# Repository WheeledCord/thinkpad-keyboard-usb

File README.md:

A PCB to allow a thinkpad laptop keyboard to be used as a USB keyboard.

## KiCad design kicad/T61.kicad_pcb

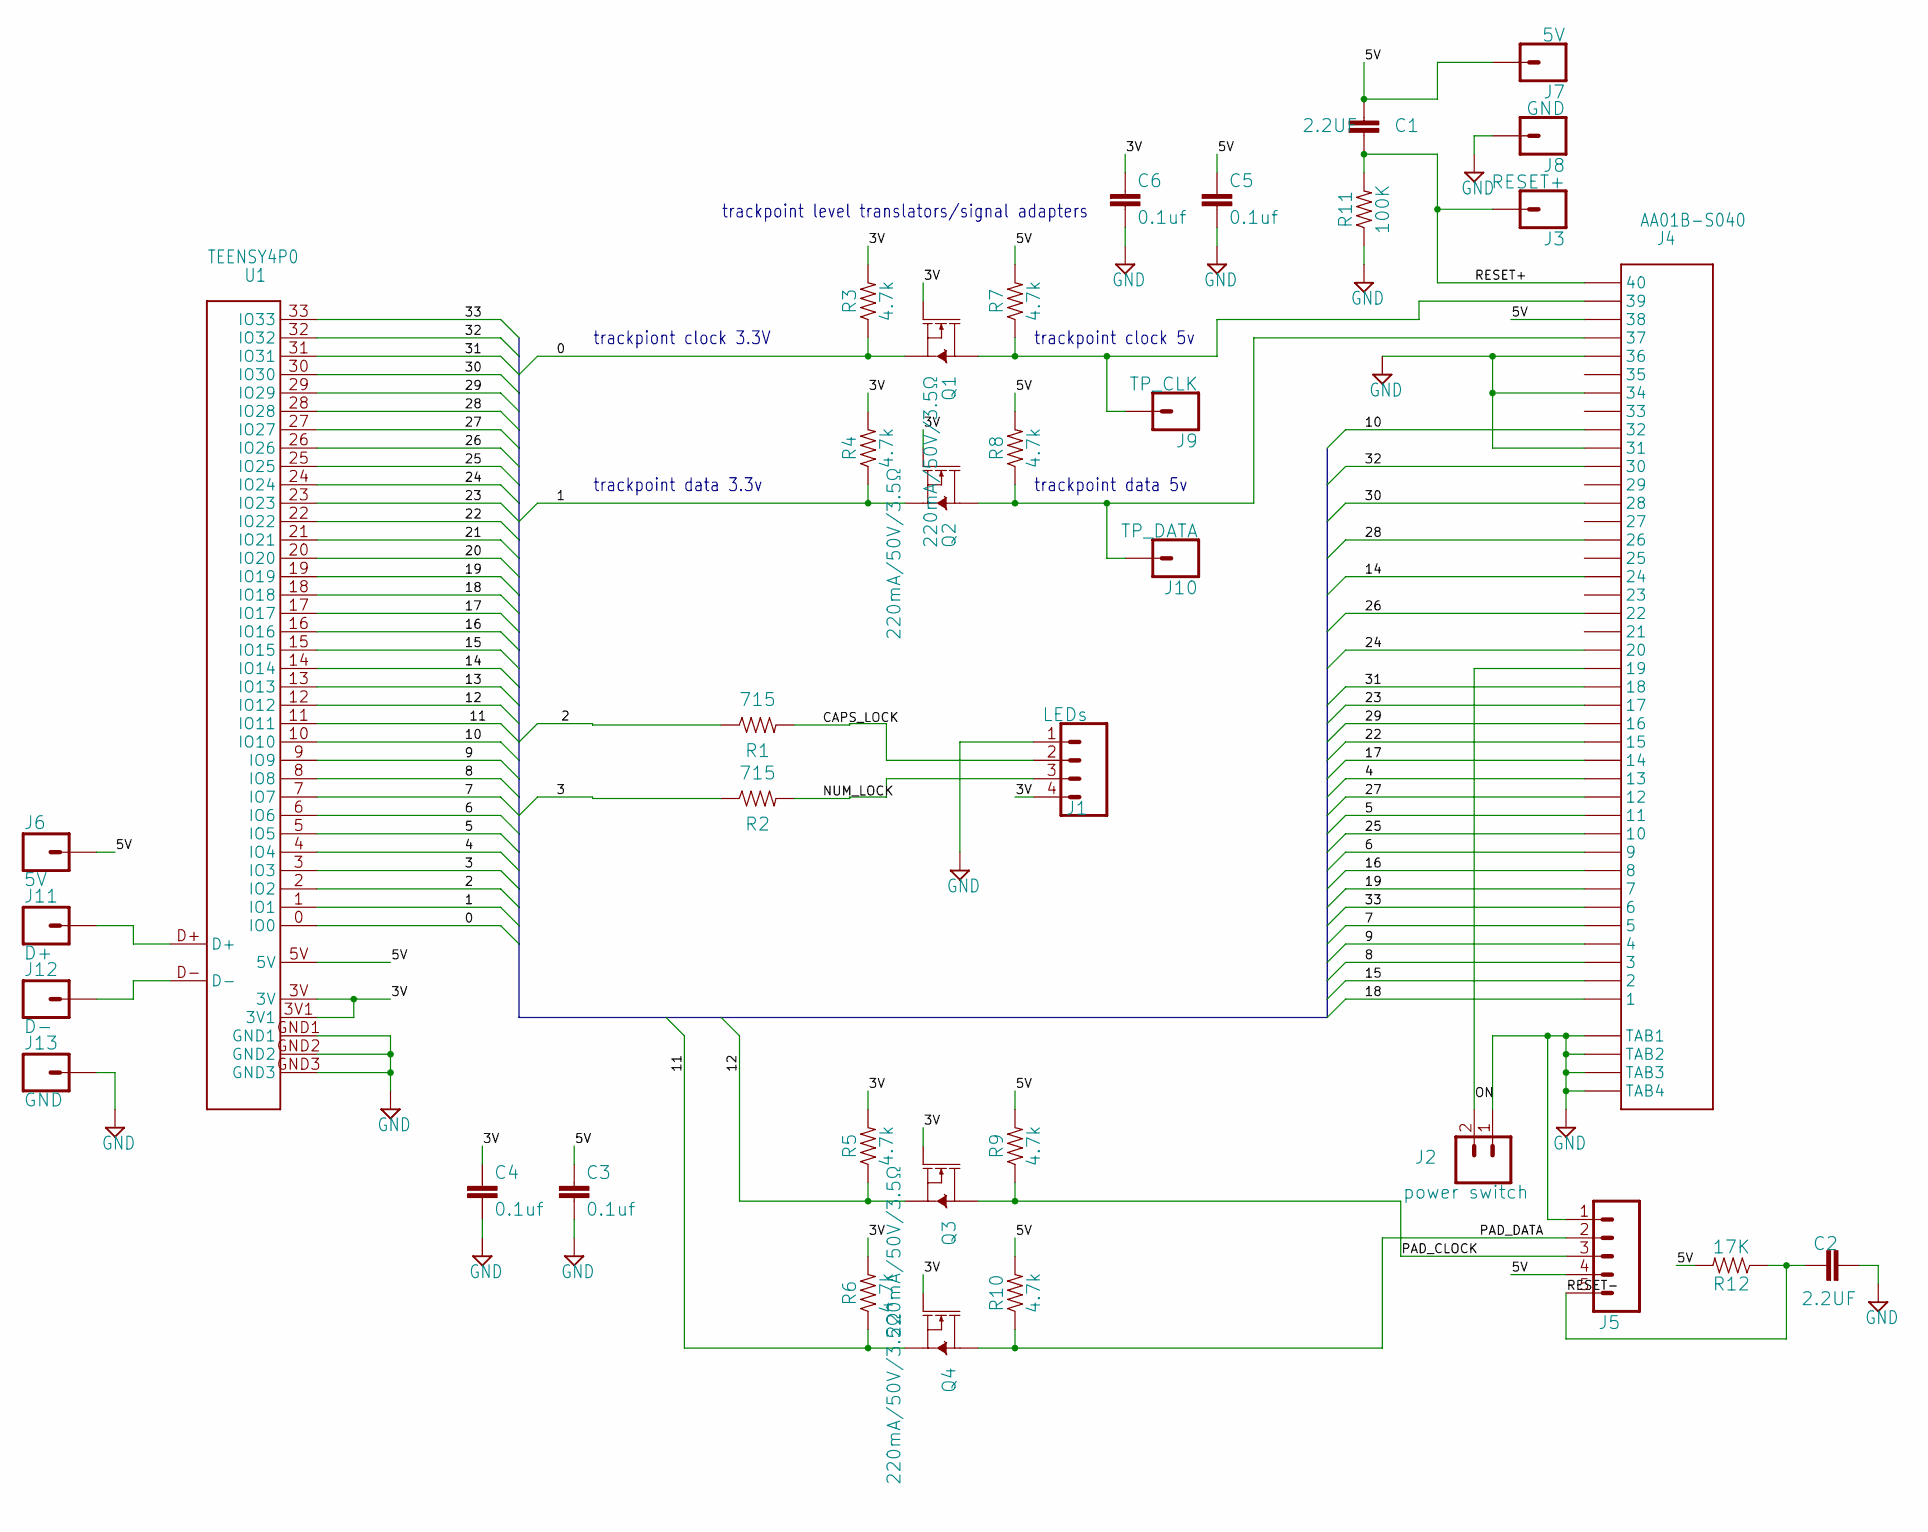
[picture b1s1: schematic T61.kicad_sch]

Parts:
C1, C2: 2.2UF; 0603_CAP
C3, C4, C5, C6: 0.1uf; 0603_CAP
J1: LEDs; 1X04
J2: power switch; 1X02
J3: RESET+; 1X01_NO_SILK
J4: AA01B-S040; WM6787_AA01B
J5: Touchpad_Signals; 1X05
J6, J7: 5V; 1X01_NO_SILK
J8, J13: GND; 1X01_NO_SILK
J9: TP_CLK; 1X01_NO_SILK
J10: TP_DATA; 1X01_NO_SILK
J11: D+; 1X01_NO_SILK
J12: D-; 1X01_NO_SILK
Q1, Q2, Q3, Q4: 220mA/50V/3.5Ω; SOT23-3
R1, R2: 715; 0603
R3, R4, R5, R6, R7, R8, R9, R10: 4.7k; 0603
R11: 100K; 0603_RESISTOR
R12: 17K; 0603_RESISTOR
U1: TEENSY4P0

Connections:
0: Q1.2 (S), R3.1, U1.0 (IO0)
1: Q2.2 (S), R4.1, U1.1 (IO1)
2: R1.1, U1.2 (IO2)
3: R2.1, U1.3 (IO3)
3V: C4.1, C6.1, J1.4, Q1.1 (G), Q2.1 (G), Q3.1 (G), Q4.1 (G), R3.2, R4.2, R5.2, R6.2, U1.3V, U1.3V1
4: J4.P$13 (13), U1.4 (IO4)
5: J4.P$11 (11), U1.5 (IO5)
5V: C1.1, C3.1, C5.1, J4.P$38 (38), J5.4, J6.1, J7.1, R7.2, R8.2, R9.2, R10.2, R12.2, U1.5V
6: J4.P$9 (9), U1.6 (IO6)
7: J4.P$5 (5), U1.7 (IO7)
8: J4.P$3 (3), U1.8 (IO8)
9: J4.P$4 (4), U1.9 (IO9)
10: J4.P$32 (32), U1.10 (IO10)
11: Q4.2 (S), R6.1, U1.11 (IO11)
12: Q3.2 (S), R5.1, U1.12 (IO12)
13: U1.13 (IO13)
14: J4.P$24 (24), U1.14 (IO14)
15: J4.P$2 (2), U1.15 (IO15)
16: J4.P$8 (8), U1.16 (IO16)
17: J4.P$14 (14), U1.17 (IO17)
18: J4.P$1 (1), U1.18 (IO18)
19: J4.P$7 (7), U1.19 (IO19)
20: U1.20 (IO20)
21: U1.21 (IO21)
22: J4.P$15 (15), U1.22 (IO22)
23: J4.P$17 (17), U1.23 (IO23)
24: J4.P$20 (20), U1.24 (IO24)
25: J4.P$10 (10), U1.25 (IO25)
26: J4.P$22 (22), U1.26 (IO26)
27: J4.P$12 (12), U1.27 (IO27)
28: J4.P$26 (26), U1.28 (IO28)
29: J4.P$16 (16), U1.29 (IO29)
30: J4.P$28 (28), U1.30 (IO30)
31: J4.P$18 (18), U1.31 (IO31)
32: J4.P$30 (30), U1.32 (IO32)
33: J4.P$6 (6), U1.33 (IO33)
CAPS_LOCK: J1.2, R1.2
D+: J11.1, U1.D+
D-: J12.1, U1.D-
GND: C2.2, C3.2, C4.2, C5.2, C6.2, J1.1, J2.1, J4.P$31 (31), J4.P$34 (34), J4.P$36 (36), J4.TAB1, J4.TAB2, J4.TAB3, J4.TAB4, J5.1, J8.1, J13.1, R11.1, U1.GND1, U1.GND2, U1.GND3
NUM_LOCK: J1.3, R2.2
ON: J2.2, J4.P$19 (19)
PAD_CLOCK: J5.3, Q3.3 (D), R9.1
PAD_DATA: J5.2, Q4.3 (D), R10.1
RESET+: C1.2, J3.1, J4.P$40 (40), R11.2
RESET-: C2.1, J5.5, R12.1
TP_CLK: J4.P$39 (39), J9.1, Q1.3 (D), R7.1
TP_DATA: J4.P$37 (37), J10.1, Q2.3 (D), R8.1

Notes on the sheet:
trackpoint data 5v
trackpiont clock 3.3V
trackpoint level translators/signal adapters
trackpoint clock 5v
trackpoint data 3.3v

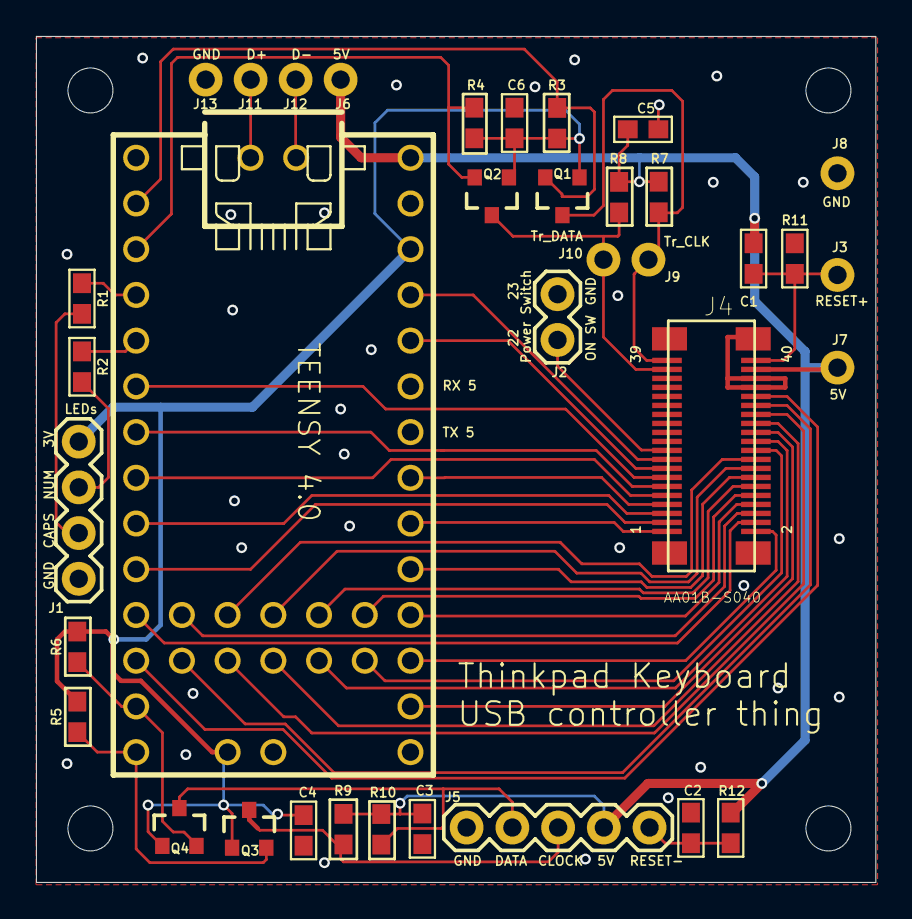
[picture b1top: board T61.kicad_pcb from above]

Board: 2 copper layers, 46.6 x 47.0 mm, 40 parts (0 on the bottom side), 45 nets.

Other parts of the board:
UNK_HOLE_0: dummyfp0
UNK_HOLE_1: dummyfp1
UNK_HOLE_2: dummyfp2
UNK_HOLE_3: dummyfp3

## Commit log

2025-07-03 journel
2025-07-11 added kicad files
2025-07-11 removed junk files
2025-07-13 firmware
